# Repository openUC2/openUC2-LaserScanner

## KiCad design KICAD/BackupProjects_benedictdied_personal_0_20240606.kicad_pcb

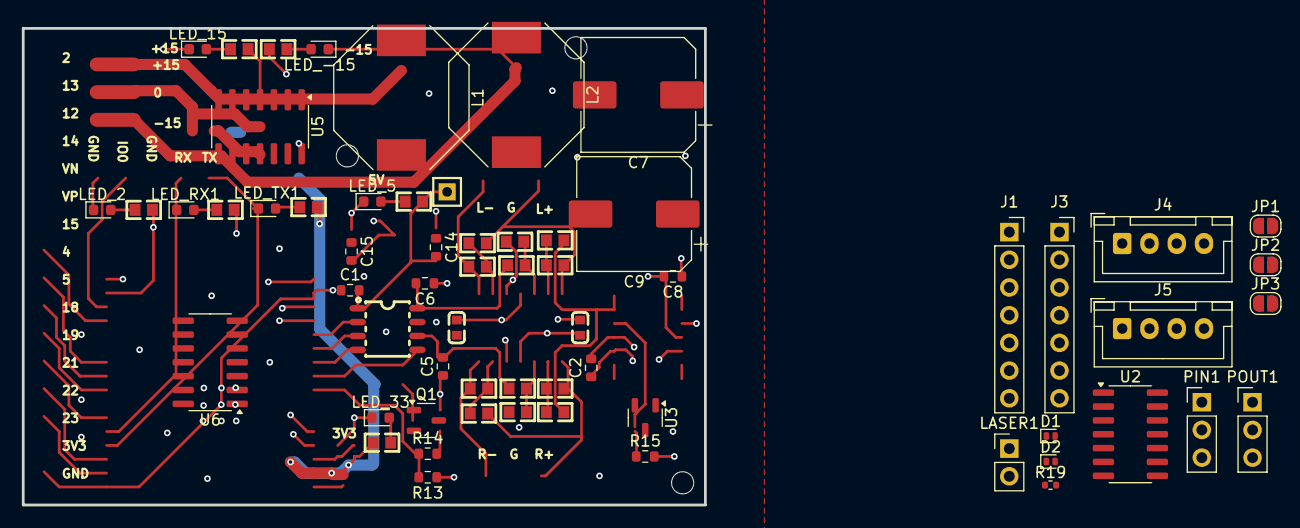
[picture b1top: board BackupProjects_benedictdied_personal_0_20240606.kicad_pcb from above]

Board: 4 copper layers, 62.5 x 43.7 mm, 65 parts (0 on the bottom side), 40 nets.

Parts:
C1, C2, C8: 100nF; R_0603_1608Metric
C5, C6: 1uF; R_0603_1608Metric
C7, C9: 1000u; CP_Elec_10x10
C13, C17: 100nF; C0603
C14, C15: 10uF; R_0603_1608Metric
D1, D2: H3V3L10B; D_SOD-882D
Hole_gge7226: Hole_gge7226
Hole_gge7231: Hole_gge7231
Hole_gge7236: Hole_gge7236
J1: xiao_single-header-1_p1-is-p1; PinSocket_1x07_P2.54mm_Vertical
J2: HDR-M-2.54_1x1; HDR-M-2.54_1X1
J3: xiao_single-header-2_p1-is-p8; PinSocket_1x07_P2.54mm_Vertical
J4, J5: XH_to-mainboard; JST_XH_B4B-XH-A_1x04_P2.50mm_Vertical
JP1: input-12V-is-5V_NO; SolderJumper-2_P1.3mm_Open_RoundedPad1.0x1.5mm
JP2: XH-direct-gpio_SDA_NO; SolderJumper-2_P1.3mm_Open_RoundedPad1.0x1.5mm
JP3: XH-direct-gpio_SCL_NO; SolderJumper-2_P1.3mm_Open_RoundedPad1.0x1.5mm
L1, L2: 10m; L_Neosid_SMs95_SMs95p
LASER1: HDR-M-2.54_1x2; PinHeader_1x02_P2.54mm_Vertical
LED_2, LED_5, LED_15, LED_33: 19-213/Y2C-CQ2R2L/3T(CY); LED_0603_1608Metric
LED_-15: 19-213/Y2C-CQ2R2L/3T(CY); LED_0603_1608Metric
LED_RX1: 19-213/Y2C-CQ2R2L/3T(CY); LED_0603_1608Metric
LED_TX1: 19-213/Y2C-CQ2R2L/3T(CY); LED_0603_1608Metric
PIN1: HDR-M-2.54_1x3; PinHeader_1x03_P2.54mm_Vertical
POUT1: HDR-M-2.54_1x3; PinHeader_1x03_P2.54mm_Vertical
Q1: AO3400A; SOT-23-3
R1, R2, R7, R8: 20K; R0603
R3, R4, R5, R6, R9, R10, R11, R12, R17, R18, R21, R22, R23, R24, R25: 10K; R0603
R13: 1M; R_0603_1608Metric
R14: 100; R_0603_1608Metric
R15: 10K; R_0603_1608Metric
R19: 1k; R_0402_1005Metric
U2, U5, U6: LM324; SOIC-14_3.9x8.7mm_P1.27mm
U3: ADR5040ARTZ-REEL7_C144273; SOT-23-3
U4: MCP4822-E/SN; SOIC-8_L4.9-W3.9-P1.27-LS6.0-BL

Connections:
3.3V: R21.2, R24.2, R25.2
3.3v: J3.5, LASER1.1
5V: C1.2, C14.2, J2.1, R23.2, U4.1
+5V: J3.7, JP1.2 (B)
+12V: J4.2, JP1.1 (A)
+15V: L1.1, PIN1.1, POUT1.1, R17.2
+VCLEAN: C2.2, C9.1, C13.2, C15.2, L1.2, R15.2
-15V: L2.1, LED_-15.2 (C), PIN1.3, POUT1.3
-VCLEAN: C7.2, C8.2, C17.2, L2.2
/CANbus_N: J4.4, JP3.2 (B)
/CANbus_P: J4.3, JP2.2 (B)
CS: J3.4, U4.2
GND: C1.1, C2.1, C5.1, C6.1, C7.1, C8.1, C9.2, C13.1, C14.1, C15.1, C17.1, D1.1 (A1), D2.1 (A1), J3.6, J4.1, J5.1, LED_2.2 (C), LED_5.2 (C), LED_15.2 (C), LED_33.2 (C), PIN1.2, POUT1.2, Q1.2 (S), R2.1, R8.1, R13.1, R18.2, U2.2 (-), U2.13 (-), U3.2 (V-), U4.7, U5.2 (-), U6.6 (-), U6.9 (-)
I2C-1_SCL: D2.2 (A2), J1.2, JP3.1 (A)
I2C-1_SDA: D1.2 (A2), J1.3, JP2.1 (A)
L: C6.2, R5.1, U4.8
L+: R7.2, R10.1, U2.7
L-: R9.2, U2.14
LASER-: LASER1.2, Q1.3 (D)
LDAC: J1.7, U4.5
LON: J3.1, R13.2, R14.1
unnamed: J1.4, J5.4
unnamed: J1.5, J5.3
unnamed: J1.6, J5.2
unnamed: Q1.1 (G), R14.2
unnamed: U6.5 (+), U6.7
unnamed: U6.8, U6.10 (+)
R: C5.2, R3.1, U4.6
R1_1: R1.1, R4.2
R2_2: R2.2, R3.2
R5_2: R5.2, R8.2
R6_2: R6.2, R7.1
R9_1: R9.1, R10.2
R11_1: R11.1, R12.2
R+: R1.2, R12.1, U2.8
R-: R11.2, U2.1
SCK: J3.3, U4.3
SDI: J3.2, U4.4
VREF: R15.1, U3.1 (V+), U3.3 (NC), U6.2 (-)
VREF_B: R4.1, R6.1, U6.1, U6.3 (+)

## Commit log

2024-03-14 Updating to simple X/Y scan
2024-05-29 ADding triggers for Frame, Line
2024-07-04 Add Kicad Drawings
2025-01-16 fixing for xiao
2025-02-06 Fix latest state
2025-02-19 updating kicad
2025-02-19 rearranging files
2025-03-10 pushing last pushing latest changes
2025-03-10 reverting to older version
2025-03-18 reverting changes from old commit
2025-03-19 Increase FREERTOS_HZ to 1000 and snake line scanning
2025-03-21 Updating to latest changes from Bene
2025-06-03 working solution for FLIM
2025-06-06 changes to make it faster without that flimlabs recognizes it yet
2025-06-07 making system faster and adding pinassignment of new uc2 galvo board
2025-06-12 change params
2025-08-13 minimal example for linescanning
2025-10-13 Initial plan
2025-10-13 Implement serial JSON interface for galvo scanner control
2025-10-13 Add documentation and test script for serial interface
2025-10-13 Add implementation notes and complete documentation
2025-10-13 Add SNAKE parameter for optimized snake scanning pattern
2025-10-14 Add persistent storage and /galvo_get command for parameter retrieval
2025-10-14 Add X/Y offsets, separate step sizes, and individual trigger enables
2025-10-14 Enable real-time parameter changes by rendering one frame at a time
2025-10-14 Update default scan parameters and documentation
    Adjusted default values for X_MAX, Y_MAX, STEP_X, STEP_Y, tPixelDwelltime, and nFrames in main.cpp and loadParameters to match updated requirements. Updated IMPLEMENTATION_NOTES.md to reflect new com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
2025-10-14 Add SIM (Structured Illumination) mode with vertical pattern shifting
2025-10-14 cleanup
2025-10-14 Add SINGLE mode for stationary galvo positioning
2025-10-14 add docs
2025-10-14 Adjust scan resolution and update ESP-IDF version
    Reduced X_MAX and Y_MAX from 2000 to 1024 and decreased STEP from 20 to 10 in main.cpp to increase scan resolution. Updated comments and added an optional delay in SPIRenderer.cpp for jitter testing.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
2025-10-15 Add binary point cloud transfer mode with Python uploader
2025-10-16 Refactor drawFrame for improved scanning logic
    Rewrote the drawFrame function to clarify and optimize scanning logic, including improved handling of SNAKE and SIM modes, trigger management, and SPI transactions. Replaced esp_rom_delay_us with ets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
2025-10-17 Improve SPI renderer frame drawing and GPIO triggers
    Refactored SPIRenderer::drawFrame for more efficient and atomic GPIO trigger handling, added fast GPIO helpers, and improved DAC value clamping. Updated documentation with new /galvo_act examples and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
2026-01-09 Adding light-sheet capability
2026-01-16 integrating light-sheet mode
2026-01-22 first working solution with new SPI schema
2026-01-23 modularization
2026-01-24 add proper triggering
2026-01-24 changing minor parameters
2026-02-03 adding bidirectional scanning
2026-02-03 good working parameters for flimlabs?
2026-02-04 Consolidate triggers; add timing overrun logging
    Remove per-pixel dwell delay and refactor trigger logic to ensure precise, periodic triggering. The pixel trigger API no longer takes a dwell_us; GPIO toggles alone provide sufficient pulse width. Ti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
